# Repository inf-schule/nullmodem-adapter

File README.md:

# Nullmodem-Adapter

Dieses Repository beinhaltet Baupläne für einen Nullmodem-Adapter, der im Kapitel [Kommunikation in Rechnernetzen - Bitübertragung und Sicherung](https://inf-schule.de/@/page/HNnpDFMzrLsl27Bz) auf [inf-schule.de](https://inf-schule.de) verwendet werden kann.

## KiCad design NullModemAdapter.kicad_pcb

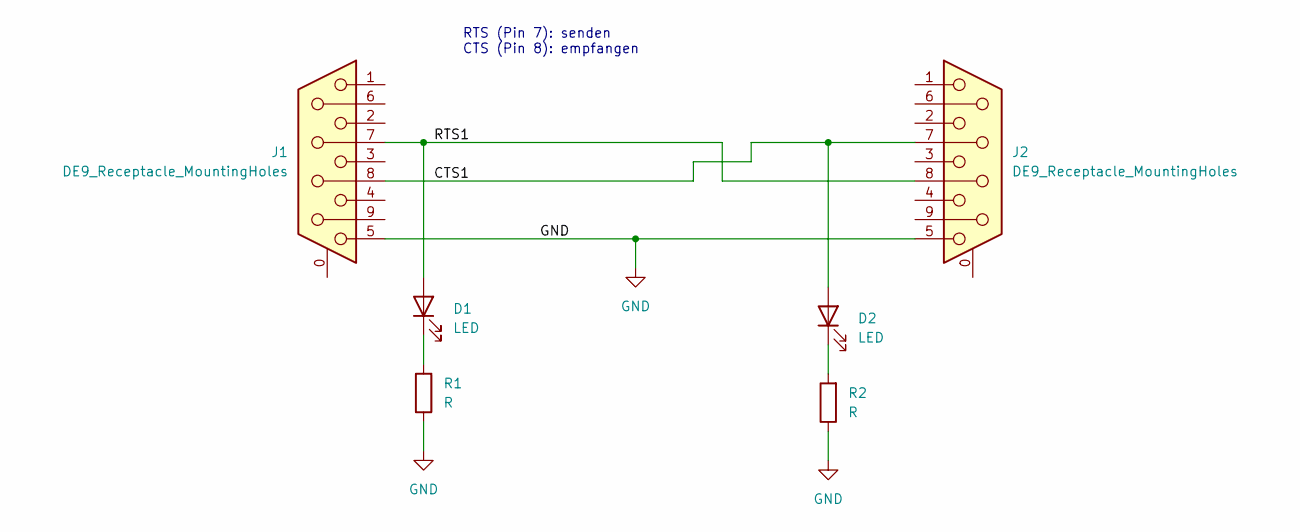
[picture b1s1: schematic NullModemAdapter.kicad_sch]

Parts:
D1, D2: LED; LED_D5.0mm
J1, J2: DE9_Receptacle_MountingHoles; DSUB-9_Female_Horizontal_P2.77x2.84mm_EdgePinOffset7.70mm_H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
R1, R2: R; R_Axial_DIN0207_L6.3mm_D2.5mm_P10.16mm_Horizontal

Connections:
/CTS1: D2.2 (A), J1.8, J2.7
/RTS1: D1.2 (A), J1.7, J2.8
GND: J1.5, J2.5, R1.1, R2.1
unnamed: D1.1 (K), R1.2
unnamed: D2.1 (K), R2.2

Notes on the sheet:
RTS (Pin 7): senden CTS (Pin 8): empfangen

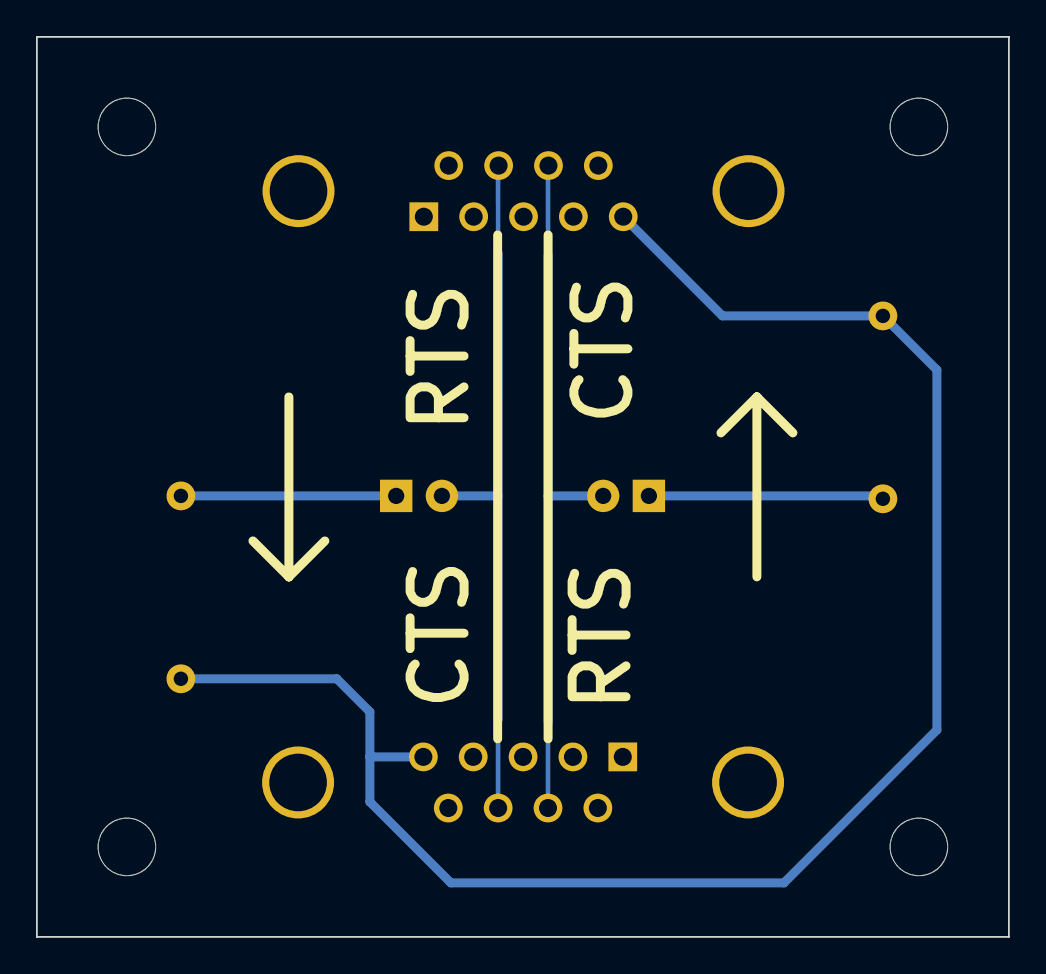
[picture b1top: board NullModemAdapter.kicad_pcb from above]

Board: 2 copper layers, 54.0 x 50.0 mm, 6 parts (0 on the bottom side), 5 nets.

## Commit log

2023-09-10 Prototyp
2024-07-04 Readme
2024-08-02 Leiterbahnen dicker und auf Unterseite
